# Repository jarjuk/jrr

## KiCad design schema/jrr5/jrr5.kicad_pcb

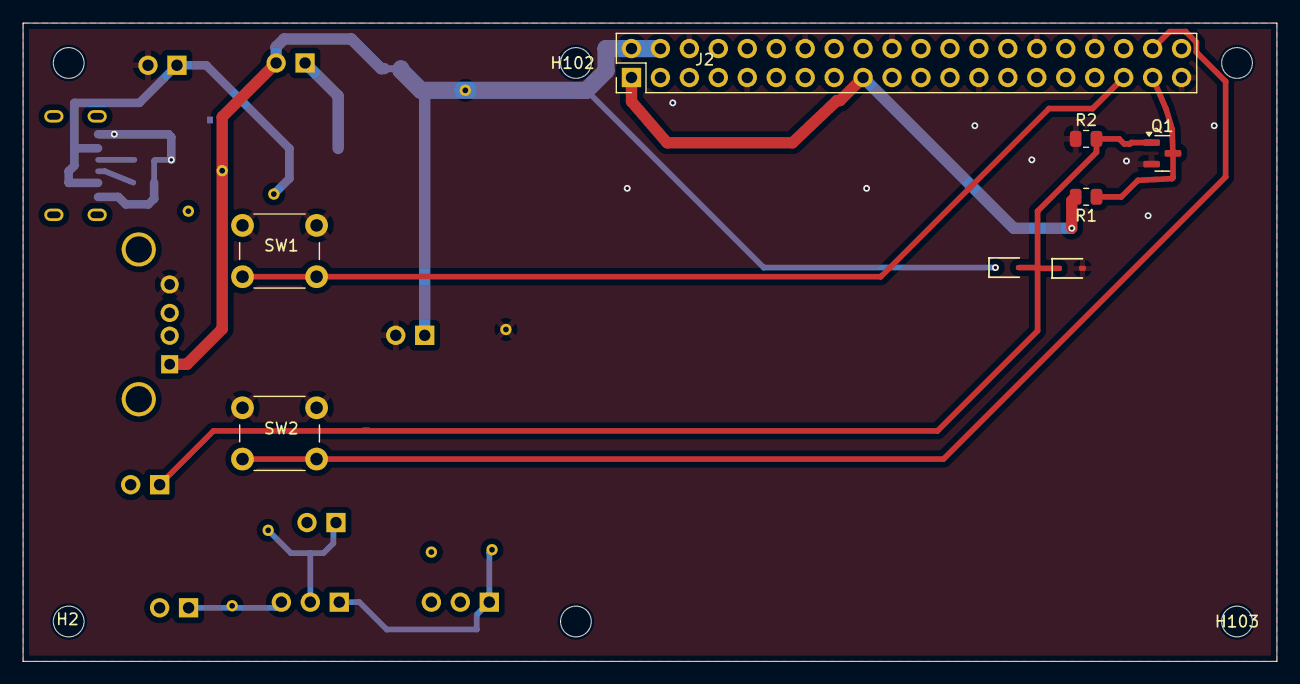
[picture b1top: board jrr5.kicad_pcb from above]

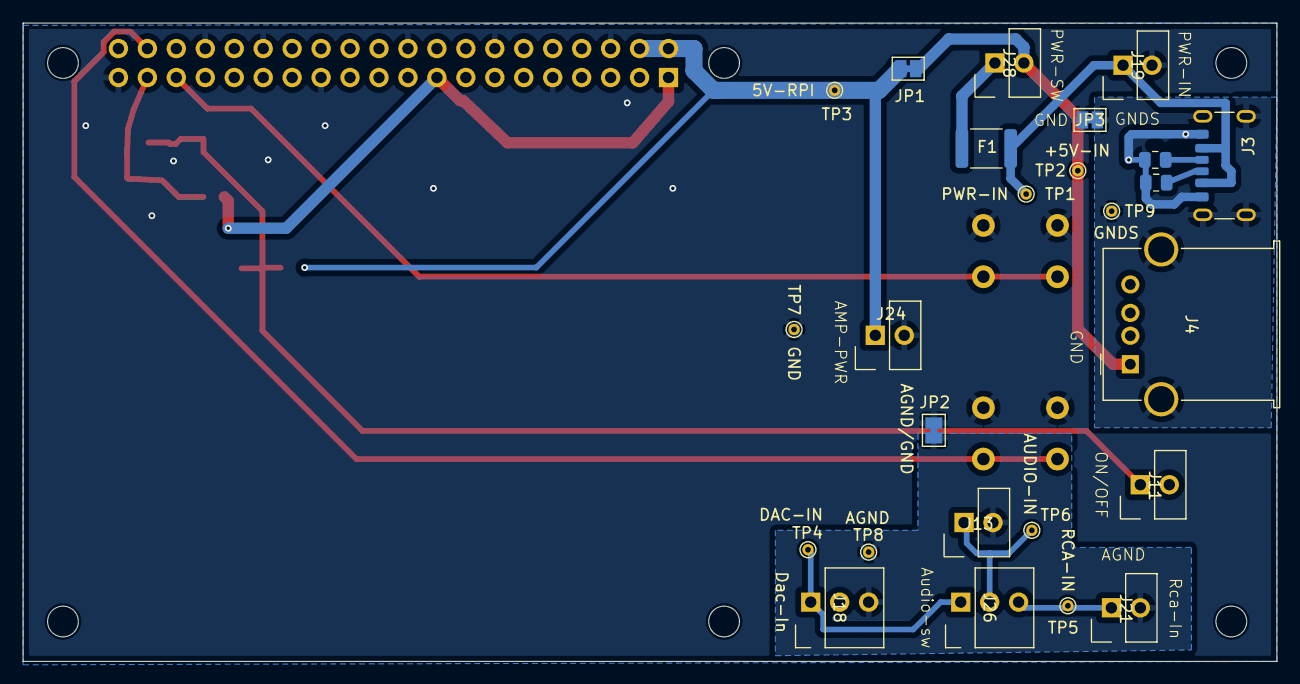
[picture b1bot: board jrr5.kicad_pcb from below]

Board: 2 copper layers, 110.0 x 56.0 mm, 39 parts (25 on the bottom side), 17 nets.

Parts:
D1, D2: Schottky,15mA; D_SOD-323
F1: 1.1A/polyfuse; Fuse_1812_4532Metric
H1, H2, H101, H102, H103, H104: MountingHole; MountingHole_2.7mm_M2.5
J2: Raspberry_Pi_2_3_GPIO; PinHeader_2x20_P2.54mm_Vertical
J3: USB-C,6Pin; USB_C_Receptacle_GCT_USB4125-xx-x-0190_6P_TopMnt_Horizontal
J4: USB-Afm,THT; USB_A_Molex_67643_Horizontal
J11, J13, J19, J21, J24, J28: Wafer,1x2,m; Wafer_1x02_P2.54mm_Vertical_male
J18, J26: Wafer,1x3,m; Wafer_1x03_P2.54mm_Vertical_male
JP1: 5V-IN/5V-RPI; SolderJumper-2_P1.3mm_Bridged_Pad1.0x1.5mm
JP2: AGND/GND; SolderJumper-2_P1.3mm_Bridged_Pad1.0x1.5mm
JP3: GND/SGND; SolderJumper-2_P1.3mm_Bridged_Pad1.0x1.5mm
Q1: BSS138; SOT-23
R1, R2: 100k; R_0805_2012Metric
R3, R4: 5k1; R_0805_2012Metric
SW1, SW2: SW_PUSH_THT_6mm; SW_PUSH_6mm
TP1: PWR-IN; TestPoint_THTPad_D1.0mm_Drill0.5mm
TP2: +5V-IN; TestPoint_THTPad_D1.0mm_Drill0.5mm
TP3: 5V-RPI; TestPoint_THTPad_D1.0mm_Drill0.5mm
TP4: Dac-In; TestPoint_THTPad_D1.0mm_Drill0.5mm
TP5: RCA-IN; TestPoint_THTPad_D1.0mm_Drill0.5mm
TP6: AUDIO-IN; TestPoint_THTPad_D1.0mm_Drill0.5mm
TP7: GND; TestPoint_THTPad_D1.0mm_Drill0.5mm
TP8: AGND; TestPoint_THTPad_D1.0mm_Drill0.5mm
TP9: GNDS; TestPoint_THTPad_D1.0mm_Drill0.5mm

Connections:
+3V3: J2.1 (3V3), J2.17 (3V3), R1.2
+5V-IN: J4.1 (VBUS), J28.2, JP1.1 (A), TP2.1
+5V-RPI: D1.1, J2.2 (5V), J2.4 (5V), J24.1, JP1.2 (B), TP3.1
AGND: J13.2, J18.3, J21.2, JP2.1 (A), TP8.1
DAC-IN: J18.1, J26.1, TP4.1
GND: D2.2, J2.6 (GND), J2.9 (GND), J2.14 (GND), J2.20 (GND), J2.25 (GND), J2.30 (GND), J2.34 (GND), J2.39 (GND), J3.A12 (GND), J3.B12 (GND), J4.4 (GND), J19.2, J24.2, JP2.2 (B), JP3.1 (A), Q1.2 (S), R2.1, R3.2, R4.2, SW1.1, SW2.1, TP7.1
GNDS: J3.S1 (SHIELD), J4.5 (Shield), JP3.2 (B), TP9.1
unnamed: J2.35 (GPIO19/MISO1), SW1.2
unnamed: J2.38 (GPIO20/MOSI1), SW2.2
unnamed: J2.37 (GPIO26), Q1.3 (D), R1.1
unnamed: J3.A5 (CC1), R3.1
unnamed: J3.B5 (CC2), R4.1
unnamed: F1.2, J28.1
ON/OFF: D1.2, D2.1, J11.1, Q1.1 (G), R2.2
PWR-IN: F1.1, J3.A9 (VBUS), J3.B9 (VBUS), J19.1, TP1.1
RCA-IN: J21.1, J26.3, TP5.1
audio-in: J13.1, J26.2, TP6.1

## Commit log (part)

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2025-06-10 README.org
2025-06-10 järviradio, rondo, wrek, YLE*, WNRV
2025-06-18 cad added
2025-06-19 katon aukkojen mitoitus
2025-06-23 jrr5-E order from JLCPCB
2025-06-28 source code added
2025-07-02 VERSION added
2025-07-02 added version tag, firmware in implementation
2025-07-03 test hook
2025-07-03 post commit hook on src/VERSION?
2025-07-03 dev firwmare update
2025-07-03 version
2025-07-03 firmware resume
2025-07-03 firmware update
2025-07-03 0.0.4-alpha2
2025-07-03 0.0.4-beta1: reboot on firmware activation
2025-07-03 fix : kanavien aktiointi
2025-07-03 rele
2025-07-03 kuittaus uudelleenkäynnistykselle
2025-07-03 test
2025-07-03 0.0.4-beta6: fixed reboot
2025-07-04 - DONE: kanavien poisto toiminnon otsikko (selaa->poista)
2025-07-04 cleanup
2025-07-04 unpack processes src sub -directory
2025-07-06 devv
2025-07-07 Browser release notes
2025-07-16 milling of the roof -> issues
2025-07-16 Jyrsintäohjeet, katon jyrsintä simuloitu, muut tarkistettu
2025-07-20 cad, bom added
2025-07-20 JRR-CAD-8: katto-01-nappainreijat-pora.ngc
2026-04-14 JRR-DEV-001: Alsa volume limit -fixed
2026-04-18 JRR-DEV-002: Expect volume knob open before shutdown handler init
2026-04-19 JRR-CAD-10, JRR-CAD-11, katon jyrsintä
2026-04-19 JRR-14: R1/R2 100k->10k
2026-04-23 Jyrsintä 2026-04
2026-04-24 JRR-CAD-13: vertical speed increased
2026-04-24 JRR-DEV-003: Configurable TFT orientation
2026-04-24 icon location fixed
2026-04-25 JRR-DEV-004: Support chirp streams
2026-04-26 JR-puhe
2026-04-26 jr-puhe icon fix
2026-04-27 channel activation/deactivation fixed
2026-04-27 Menu changes
2026-04-27 Version 0.0.6
2026-04-27 Release 0.0.7
2026-04-28 0.0.8-rc02
2026-04-28 linking test
2026-04-28 screenshots addde
2026-04-28 Screeenshots to README
2026-04-28 More screenshots
2026-04-28 screenshots
2026-04-28 lisää kanavia väärin
2026-04-28 JRR-DEV-006: Factory reset
2026-04-28 rc change
2026-04-28 JRR-DEV-006: Factory reset: ohjeen päivitys
2026-04-28 0.0.8-rc06

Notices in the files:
schema/jrr5/jrr5.kicad_pcb:
${ISSUE_DATE}/©${COMPANY}
